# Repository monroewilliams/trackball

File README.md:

This is the code to run a trackball I'm building for myself.<br>

It's currently based around either a [Seeeduino XIAO](https://wiki.seeedstudio.com/Seeeduino-XIAO/) or the very similar [Adafruit QT Py](https://www.adafruit.com/product/4600), and a couple of optical mouse sensor breakout boards. I've built two so far, one using [these ADNS-9800 boards](https://www.tindie.com/products/jkicklighter/adns-9800-optical-laser-sensor/), and one using [these PMW3360 breakout boards](https://www.tindie.com/products/jkicklighter/pmw3360-motion-sensor/).

### Update January 2025 ###
As an alternative to off-the-shelf microcontrollers and sensor boards, I've created a custom main board and sensor breakouts that can be ordered from a PCB creation/assembly service (I've been using [JLCPCB](https://jlcpcb.com)). The KiCad files and the files need to order them from JLCPCB are in their own repositories on github. 

[Details on the custom boards are here.](hardware/Custom.md)

### Update January 2026 ###
I've refined the model for the main body of the trackball to be less of a brick and more of a hollow shell, which leaves much more room inside for wire routing, etc. The cable outlet at the front of the shell now also provides an option for a hard-mounted [usb-c plug](https://www.sparkfun.com/sparkfun-usb-c-breakout.html), or [similar](https://www.amazon.com/dp/B0CB2VFJ54) [clones](https://www.aliexpress.us/item/3256808121945210.html) 

I added an [updated version of the button carrier](hardware/Button-carrier-v2.md). Its design is a bit more refined overall, but the main feature is that it allows you to avoid soldering wires to the microswitch by accepting a 3-pin JST XH female connector.

I also added an option to modify the sensor transform for a left-handed build. To make use of this, print mirrored versions of the main body and bottom plate (most slicers have an option to do this at slicing time), and define LEFT_HANDED when compiling trackball.cpp to modify the sensor transform. The `env:rp2040_mwtrackball_left_handed` section in [platformio.ini](platformio.ini) demonstrates this.

<br>

## History ##

I started this project because my favorite ergonomic trackball, the Trackman Marble FX, is basically no longer viable. I really like the shape of it, but it's PS/2 only, has a number of issues with tracking and durability, and has become really hard to find/expensive. I have a small collection of them, most of which have broken over the years.<br>

I decided to build my own trackball with a shape that fits my hand similar to the old Trackman Marble FX, and incorporated a feature from the Kensington Slimblade (probably my second favorite, although not for its ergonomics): twisting the ball in the Z axis acts like a scroll-wheel (complete with clicky sounds produced by a piezo speaker).<br>

[Short video demo is here](https://www.youtube.com/watch?v=PVdwrbiuzwA)

To be able to sense rotation in all three axes, it needs to use two mouse sensors, positioned at different points around the ball. <br>

I'm quite happy with the current state of the project. I prefer using this trackball to any other I've used at this point, which is saying something. :) <br>

The [hardware](hardware) directory contains the OpenSCAD files for the printed plastics. The [src](src) directory has the code. If you want to see how all the parts fit together, you can go straight to the [assembly guide](hardware/Assembly.md). <br>

## BUILD ##

I'm building this with PlatformIO/VSCode. The root of the repository should open directly with VSCode.

I do my work on Mac OS X, so I don't know if there will be any issues using it on Windows or Linux.

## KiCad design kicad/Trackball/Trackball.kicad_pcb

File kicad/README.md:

# Board

This directory contains the [Kicad](https://kicad.org) files for a circuit board I've designed for the trackball. This is intended to take the place of the breadboard in a more permanent build.<br>

<br>

This design uses the [Seeeduino XIAO Kicad library](https://www.seeedstudio.com/blog/2020/04/23/use-seeeduino-xiao-in-kicad-pcb-design-like-a-components/), so if you want to open/modify it with Kicad you probably need to install that first.<br>

This is my first attempt at designing something with Kicad, and I really have no idea what I'm doing. I've had an initial batch of them made by [OshPark](https://oshpark.com), but I haven't actually tested them out yet, so caveat emptor, etc, etc.<br>

I also haven't yet modified the OpenSCAD files for the trackball body to have an option that will make these fit properly. I'm working on that as time allows.<br>

That being said, if you want some of these made for yourself, you can order them 3 at a time [here](https://oshpark.com/shared_projects/D077qVES).<br>

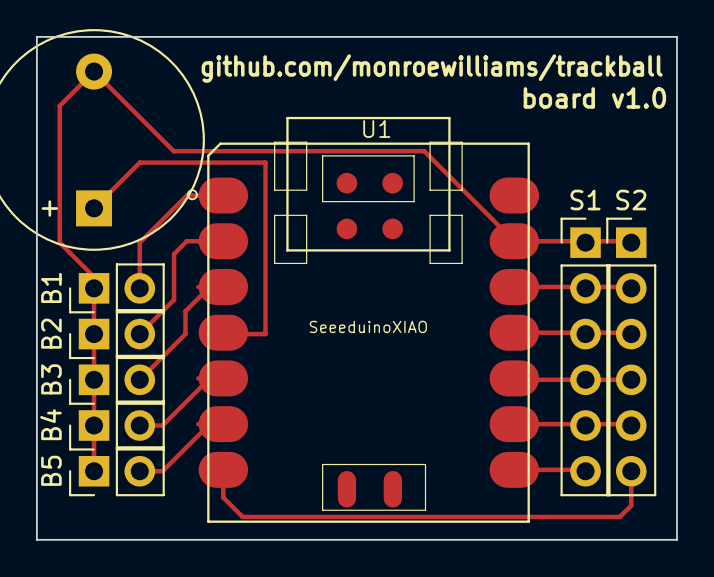
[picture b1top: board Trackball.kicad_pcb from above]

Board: 2 copper layers, 35.6 x 27.9 mm, 9 parts (0 on the bottom side), 13 nets.

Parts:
B1, B2, B3, B4, B5: Conn_01x02; PinHeader_1x02_P2.54mm_Vertical
LS1: Piezo; Buzzer_12x9.5RM7.6
S1, S2: Conn_01x06; PinHeader_1x06_P2.54mm_Vertical
U1: SeeeduinoXIAO; Seeeduino XIAO-MOUDLE14P-2.54-21X17.8MM

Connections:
GND: B1.1, B2.1, B3.1, B4.1, B5.1, LS1.2, S1.1, S2.1, U1.13
unnamed: B1.2, U1.1
unnamed: B2.2, U1.2
unnamed: B3.2, U1.3
unnamed: B4.2, U1.5
unnamed: B5.2, U1.6
unnamed: LS1.1, U1.4
unnamed: S1.2, S2.2, U1.12
unnamed: S1.3, S2.3, U1.11
unnamed: S1.4, S2.4, U1.10
unnamed: S1.5, S2.5, U1.9
unnamed: S1.6, U1.8
unnamed: S2.6, U1.7

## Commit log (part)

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2015-01-24 Initial checkin. Code is working with a single sensor and 3 buttons.
2015-01-24 Switch to using transactional SPI modes in this SPI library: https://github.com/PaulStoffregen/SPI
2015-01-24 Remove adns::init_spi(), since it now just calls SPI.begin().
2015-01-24 Add read_x() and read_y() convenience methods to adns
2015-01-24 Switch to using read_x and read_y, and a bit of cleanup.
2015-01-24 change mouse movement from interrupt-driven to polled.
2015-01-25 Add symbolic constants for delay times from the datasheet
2015-01-25 Change read_x and read_y into read_motion, which fills in member variables x and y. This is so that it can properly control reading the motion register to latch the values.
2015-01-25 Update firmware to A6 version
2015-01-25 Minor cleanup
2015-01-25 first attempt at using the burst read for motion reports. Not working yet, and I'm not sure why.
2015-01-25 Moved the chip select pin of sensor 1
2015-01-26 Added second sensor, fixed axes, and set up scrolling on twist
2015-01-26 made internal methods in adns private
2015-01-26 added set_cpi
2015-01-26 tweak cpi and scrolling rate
2015-01-26 README.md edited online with Bitbucket
2015-01-27 move piezo to pin 3
2015-01-27 tweak scrolling algorithm slightly
2015-01-28 Added build info to readme
2015-02-02 cleanup
2015-02-02 Make the duration of the click 1 millisecond, which makes it more audible.
2015-08-15 Clean up serial debug. Made it switchable with a macro in trackball.h, such that it compiles down to nothing when switched off. Moved most strings used for debug logging into flash with the F() macro.
2015-08-15 More serial cleanup
2015-08-15 Add support for the new pluggable HID/USB modules in Arduino 1.6.6
2021-01-09 Fix a couple of warnings.
2021-01-09 Update debug output a bit.
2021-01-18 Debug logging tweaks.
2021-01-29 Rename main .ino file to .cpp, simplify include directives.
2021-01-31 Factor out pin assignments in preparation for changing boards.
2021-01-31 Fix a sign-extension bug in adns.
2021-02-02 Converted to use Seeeduino XIAO cpu, which required converting from the Mouse library to Adafruit_TinyUSB.
2021-02-02 New sensor location
2021-02-02 Scroll resolution multiplier option.
2021-02-07 Update reported product descriptor string
2021-02-07 Fix a dumb bug in the button polling code.
2021-02-07 Limit updates to every 8ms (~120hz)
2021-02-09 Flatten file hierarchy.
2021-02-09 First attempt at full model.
2021-02-09 remove render() calls from trackball.scad. They can be selectively added to the test file as needed.
2021-02-09 Add clearance to body_right_cut() so the ball can get in and out (oops...)
2021-02-09 Added front/rear overhang parameters to button_params.
2021-02-09 Playing with using quaternions to calculate the actual ball rotation, instead of the current hacky sensor fusion.
2021-02-10 Next iteration, as printed.
2021-02-11 Added readme in the hardware directory.
2021-02-11 refined shape and button placements added cutout under handrest for the breadboard added breadboard cutout test file
2021-02-12 Fix typo that crept into the microswitch scad somehow.
2021-02-12 Another round of changes on the trackball scad.
2021-02-13 Disable resolution multiplier for scroll, and turn the scroll tick down a bit.
2021-02-13 Separate the switch to enable/disable scroll resolution from a separate switch to use a custom HID descriptor. Added some experimental code that tries to fuse the sensor data more accurately using tr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
2021-02-16 Enlarge the ball removal clearance cut slightly.
2021-02-16 add prender() module
2021-02-16 Minor test change
2021-02-16 Fix unintentional cut on front left. Factor out body_right_cut_translation() for future experiments.
2021-02-16 Another shape revision.
2021-02-16 Fix click bug.
2021-02-17 Bigger breadboard cutout and bigger wire junction cutouts near breadboard.
2021-02-18 Run sensors at higher cpi and scale down. This will help with more accurate angle calculations later.
2021-02-18 Invert both sensors for improved wire routing.
2021-02-18 Added bottom_cover() with attachment studs and matching stud holes in the full body.
2021-02-18 Made rcube treat negative height the same as ccube.
2021-02-19 Drive the piezo with the tone() function, making it _much_ louder.
2021-02-20 Hardware readme update to add info about alternate ball.
2021-02-25 Many changes to trackball.scad: - added option for pmw3360 sensor shape - changed sensor mount screw holes to accept 2mm machine screws - tweaked several things to be based on the ball diameter, to w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
2021-02-26 Fix a problem with the ball-removal clearance cut interfering with the bearing fit.
2021-02-26 Moved piezo to pin 3 to free up i2c port Switch from XIAO to Adafruit QT Py brought in NeoPixel library and set up the on-board pixel of the QT Py Changed the tone for the scrolling click to one that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
2021-02-26 Change x/y deltas in the USB descriptor and report to be 16 bit, so they can't overflow/underflow (it's easy to exceed +/-127 per report when flicking the ball quickly).
2021-02-26 Fix burst motion read.
2021-02-26 Expose all data read by the burst motion read via member variables.
2021-02-26 Updates to hardware readme
2021-02-26 A lower delay seems to work fine in the pixel burst read loop.
2021-02-26 Sensor image blit loop is no longer a source of shame.
2021-02-27 Added support for reading images from the sensors and displaying it on an SSD1327 display connected over i2c Cleaned up debug logging Organized configuration switches at the top of trackball.cpp Made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
2021-02-27 Add support for SSD1351 display connected over SPI.
2021-03-01 Added support for PMW3360 sensor.
2021-03-01 Added option to not include button supports when printing the bottom cover. Defaults to omitting them.
2021-03-02 Add photo of button.
2021-03-03 Add assembly photos
2021-03-03 Added assembly guide.
2021-03-03 One more readme update.
2021-03-03 Add some screenshots of the OpenSCAD model to the assembly guide.
2021-03-03 Reorganized trackball.scad slightly to put the most useful bits at the top.
2021-03-03 More proofreading edits.
2021-03-03 One more thing.
2021-03-03 gah... spelling.
2021-03-03 Youtube embedding fail.
2021-03-03 add prototype photos
2021-03-03 Fix a minor misprint in the assembly guide
2021-03-07 Made the layout when drawing the sensor images more dynamic.
2021-03-10 Add .stl files for the version of the trackball shown in the assembly guide. Specs: 55mm ball diameter pmw3360 sensors 10 degree sensor skew angle
2021-03-11 Renamed body_height and body_diameter to clarify that they're only used by body_minimal().
2021-03-11 Made button_cutout() more closely fit the profile of the front overhang.
2021-03-11 Added a param to button_params to allow disabling the button supports per-button. Refined third (alternate thumb) button placement. Added stl files for the refined button version of the main body and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
2021-03-11 Added a thicker (3mm vs. 2mm) version of the bottom cover stl. Renamed the existing bottom cover stl to reflect the fact that it doesn't depend on the sensor type.
2021-04-28 Add a bit more clearance around the aft sensor.
2021-04-28 Adjust some of the $f* parameters to increase faceting on the outer shell, to make the printed part look smoother.
2021-05-02 Updated stls for the 55mm model and base plate to incorporate updates.
2021-05-05 Reworked the bottom plate mounting holes to make the fit more tolerant of slight first-layer squish. Added the ability to secure the bottom plate with screws. Moved one of the holes slightly to give 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
2021-05-05 Leaving the piezo pin in OUTPUT mode all the time was causing a faint, annoying noise from the piezo speaker. Don't do that.
2021-05-05 Remove some obsolete STLs.
2021-05-05 Add Kicad source for the circuit board design.
2021-09-12 My Mods
    -Added support for PMW3389
    -Added feature for adjusting CPI if holding down MB 3 while scrolling
    -various changes to default code (different pin for buzzer, MB 4 and MB 5 included in USB HID report)
2022-02-14 Set the HID string descriptor (in addition to the product descriptor).
2022-02-14 Default to not using a custom HID descriptor. This makes the trackball a bit more compatible, as it conforms to the boot mouse protocol.
2022-02-14 Adjustments to TinyUSB library setup, to work properly on both XIAQ and QT Py.
2022-02-14 Refactor some of the OpenSCAD code slightly, and add .scad files showing how each of the .stl files was generated.
2022-02-19 Trackball renders under openscad nightly
    Closes #2
    I don't see a difference in the model before and after, but I am still
    getting used to how this design looks.
    The reason why I wanted this:
    ```
    $ time openscad hardware/trackball.scad -o trackball.stl # OpenSCAD version 2019.05
2022-10-03 PMW3389 sensor support, courtesy of https://github.com/JPJrunesJPJ .
2022-10-03 The code which set up the sensor's CPI register(s) was completely wrong, and needed to do different things for each sensor model. At the moment I've only tested the codepath for the pmw3360, as that'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
2024-12-18 Updated some platformIO library references for the current state of platformIO. Added a case to platformio.ini for the QT Py RP2040. Builds but doesn't seem to work correctly yet, needs investigation.
2024-12-23 Now fully functional on the QT Py RP2040.
2025-01-01 Comment out hard-coded upload_port and monitor_port directives in platformio.ini, since these are system-specific. Update a couple comments in platformio.ini.
2025-01-01 Make the NeoPixel on Adafruit boards a much dimmer purple.
2025-01-14 Updates for the second run of custom boards.
2025-01-14 Additional clearance for the new custom pmw3360 board.
2025-01-14 Make breadboard tabs and the left-side breadboard access cutout optional.
2025-01-14 Make clearance for the custom sensor boards optional
2025-01-19 Add info about custom boards. Add hollow version of the trackball model.
2025-01-22 Fix a couple of faults in the new hollow shell model.
2025-02-15 Add BUTTON_LIGHTS option, which lights up the NeoPixel when buttons are pressed and fades after they're released.
2025-02-15 Add an env in platformio.ini to set up source-level debugging on the custom trackball board using the RP Debug Probe.
2025-02-15 Major revision to the microswitch carrier, I'm calling it version 2. The original version is still in the repository for those who might prefer it.
    The carrier now prints in two pieces, and you have the option of either soldering wires directly to the switch as before, or using a 3 pin JST-XH plug in the back of the carrier.
    It turns out that the spacing of pins 1 and 3 in the JST-XH exactly line up with the "common" and "normally-open" pins on the switch, and the carrier has the correct shape for the keyed connector to 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
2025-02-15 Updates to the hollow trackball model: Now supports using a small USB-C breakout board (roughly 12x15mm, available from Amazon or AliExpress) instead of a fixed cable.
    Updates to the main trackball model:
    bottom screws are now optional.
    Minor cleanup of $fn directives in both files.
    Cleaned up some of the old STLs and moved their corresponding .scad files to a "deprecated" directory to avoid confusion.
2025-02-15 Minor readme updates
2025-02-16 Disabling the USB plug by default for now. I hadn't done a full test print yet, and when I did I found that the placement interferes with the front sensor wires. Also, the breakout board doesn't seem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
2025-02-27 Updates to the main shell: - reduced the size of the access cutouts for the sensor screws a bit (from 5mm to 3mm diameter -- should be plenty of room for a 1.5mm allen wrench for the M2 screws) - the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
2026-01-04 Add an option for a left-handed build. Add a define to allow platformio.ini to override the default device name in the descriptor.
2026-01-04 Update readme with info about v2 switch carrier and left-handed build option.
2026-04-15 Another readme update.
